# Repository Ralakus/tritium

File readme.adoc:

= Tritium Project
An open source RISC based balanced ternary computer research project

== This is a research project
This project is not fully intended to get a perfectly functional computer out to the market, but rather, it is intended to get the concept of ternary computing out to the public so more people will start researching ternary computing as an alternative to binary computing. 

== What does balanced ternary mean?
Normal computers process data in binary which means two states, a one and a zero. Ternary is similar except operating on three states. In balanced ternary, there is a negative (i), neutral (0), and positive (1) which means numbers are naturally signed thus simplifying the architecture and general logic. Ternary also has the best radix efficiency for any integer base of 1.0046 where binary is 1.0615 with base e, 1.0000 being the most efficient. A 'trit' is the ternary analogue of a bit which stores an i (-1), 0, or 1. 

== Has this been done before?
There are many projects similar to this but they either haven't gone very far, closed source and secretive, or dead. The main inspiration for this project is the Russian Setun computer, more specifically the Setun-70 which has an 18 trit word and 81 words of memory with a magnetic drum holding more memory. 

== Directory Structure
* docs - contains documentation on the project and lab results
* kicad - contains the kicad project files for each part
** components - contains all complex multigate circuits
** gates - contains all ternary gates and their panelized PCBs
** logic - contains logical schematics of circuits using logic gates instead of transistors
* library - contains all of the kicad libraries such as the footprints, spice models, and symbols

== Possible final computer variants
=== Tritium-6
A 6-trit computer that is cheap and simple to make where the instructions more closely resemble microcode rather than instructions.

==== Design Goals
* Around or less than $250 in components
* Have the ability to communicate with binary components
* Use easily sourcable parts
* One clock cycle per instruction

=== Tritium-27
A full scale computer that mirrors RISC-V in capability and instruction set.

==== Design Goals
* Around or less than $1000 in components
* Have the ability to communicate with binary components
* Use easily sourcable parts

== Current Status
The gates from OSHPark came but I've hit a bit of a time and financial crunch so I don't quite have the time to work on the physical part of the project. I'm currently working with a local college professor to write up a better ISA than the previous versions for a machine that I could follow that wouldn't be too expensive to implement. I've decided that the decoding logic for the control module may be too expensive to implement so I will see if I can use a binary EEPROM using encoded balanced ternary as a lookup table and then convert the inputs back to native balanced ternary.

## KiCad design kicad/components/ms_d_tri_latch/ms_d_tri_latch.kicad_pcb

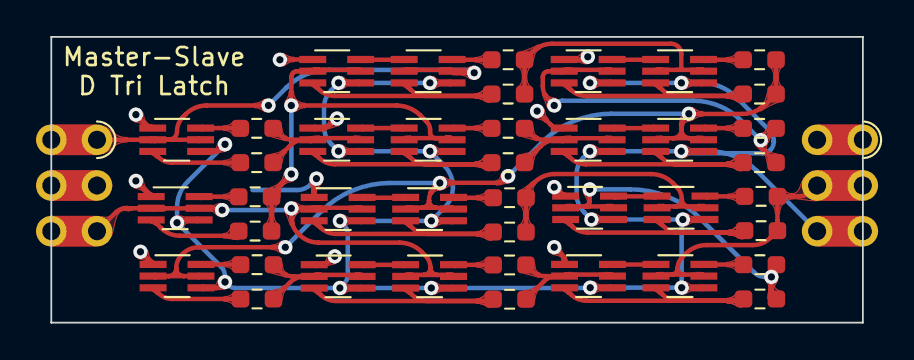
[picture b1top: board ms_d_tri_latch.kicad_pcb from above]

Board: 2 copper layers, 45.1 x 15.9 mm, 43 parts (0 on the bottom side), 45 nets.

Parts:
J1, J2: Conn_01x03; Hybrid_Castellation_1x03_P2.54
Q1, Q2, Q3, Q4, Q5, Q6, Q7, Q8, Q9, Q10, Q11, Q12, Q13, Q14, Q15, Q16, Q17, Q18, Q19: BSS8402DW-7-F; SOT-363_SC-70-6_Handsoldering
R1, R2, R3, R4, R5, R6, R7, R8, R9, R10, R11, R12, R13, R14, R15, R16, R17, R18, R19, R20, R21, R22: 12k; R_0603_1608Metric_Pad0.98x0.95mm_HandSolder

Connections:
/Inverter2/Nti: Q19.6 (D), R22.2
/Inverter2/Out: Q14.2 (G), Q14.5 (G), Q15.2 (G), Q15.5 (G), R21.2, R22.1
/Inverter2/Pti: Q19.3 (D), R21.1
/d_latch1/Antimin4/B: Q3.2 (G), Q3.5 (G), R19.2, R20.1
/d_latch1/Antimin5/Out: Q4.2 (G), Q4.5 (G), R7.2, R8.1
/d_latch1/Antimin7/B: Q18.2 (G), Q18.5 (G), R1.2, R2.1
/d_latch1/Inverter1/Nti: Q1.6 (D), R2.2
/d_latch1/Inverter1/Pti: Q1.3 (D), R1.1
/d_latch1/~Q: Q5.2 (G), Q5.5 (G), R3.2, R4.1
/d_latch/Antimin4/B: Q10.2 (G), Q10.5 (G), R17.2, R18.1
/d_latch/Antimin5/Out: Q11.2 (G), Q11.5 (G), R15.2, R16.1
/d_latch/Antimin7/B: Q16.2 (G), Q16.5 (G), R9.2, R10.1
/d_latch/Inverter1/Nti: Q8.6 (D), R10.2
/d_latch/Inverter1/Pti: Q8.3 (D), R9.1
/d_latch/Q: Q1.2 (G), Q1.5 (G), Q6.2 (G), Q6.5 (G), Q9.2 (G), Q9.5 (G), R13.2, R14.1
/d_latch/~Q: Q12.2 (G), Q12.5 (G), R11.2, R12.1
D: J1.1, Q8.2 (G), Q8.5 (G), Q13.2 (G), Q13.5 (G)
Enable: J1.3, Q7.2 (G), Q7.5 (G), Q17.2 (G), Q17.5 (G), Q19.2 (G), Q19.5 (G)
unnamed: Q2.1 (S), Q3.6 (D)
unnamed: Q2.3 (D), Q3.3 (D), R3.1
unnamed: Q2.6 (D), R4.2
unnamed: Q4.1 (S), Q5.6 (D)
unnamed: Q4.3 (D), Q5.3 (D), R5.1
unnamed: Q4.6 (D), R6.2
unnamed: Q6.1 (S), Q7.6 (D)
unnamed: Q6.3 (D), Q7.3 (D), R7.1
unnamed: Q6.6 (D), R8.2
unnamed: Q9.6 (D), R12.2
unnamed: Q9.3 (D), Q10.3 (D), R11.1
unnamed: Q9.1 (S), Q10.6 (D)
unnamed: Q11.1 (S), Q12.6 (D)
unnamed: Q11.3 (D), Q12.3 (D), R13.1
unnamed: Q11.6 (D), R14.2
unnamed: Q13.1 (S), Q14.6 (D)
unnamed: Q13.3 (D), Q14.3 (D), R15.1
unnamed: Q13.6 (D), R16.2
unnamed: Q15.1 (S), Q16.6 (D)
unnamed: Q15.3 (D), Q16.3 (D), R17.1
unnamed: Q15.6 (D), R18.2
unnamed: Q17.1 (S), Q18.6 (D)
unnamed: Q17.3 (D), Q18.3 (D), R19.1
unnamed: Q17.6 (D), R20.2
Q: J2.2, Q2.2 (G), Q2.5 (G), R5.2, R6.1
VDD: J2.3, Q1.4 (S), Q2.4 (S), Q3.4 (S), Q4.4 (S), Q5.4 (S), Q6.4 (S), Q7.4 (S), Q8.4 (S), Q9.4 (S), Q10.4 (S), Q11.4 (S), Q12.4 (S), Q13.4 (S), Q14.4 (S), Q15.4 (S), Q16.4 (S), Q17.4 (S), Q18.4 (S), Q19.4 (S)
VSS: J1.2, J2.1, Q1.1 (S), Q3.1 (S), Q5.1 (S), Q7.1 (S), Q8.1 (S), Q10.1 (S), Q12.1 (S), Q14.1 (S), Q16.1 (S), Q18.1 (S), Q19.1 (S)

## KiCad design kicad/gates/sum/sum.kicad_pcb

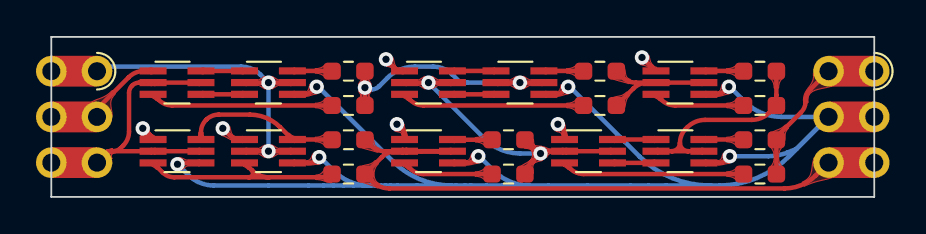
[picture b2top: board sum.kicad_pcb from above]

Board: 2 copper layers, 45.7 x 8.9 mm, 24 parts (0 on the bottom side), 28 nets.

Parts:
J1, J2: Conn_01x03; Hybrid_Castellation_1x03_P2.54
Q1, Q2, Q3, Q4, Q5, Q6, Q7, Q8, Q9, Q10: BSS8402DW-7-F; SOT-363_SC-70-6_Handsoldering
R1, R2, R3, R4, R5, R6, R7, R8, R9, R10, R11, R12: 12k; R_0603_1608Metric_Pad0.98x0.95mm_HandSolder

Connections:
/Inverter BL/Nti: Q8.6 (D), R10.2
/Inverter BL/Out: Q4.2 (G), Q4.5 (G), Q6.2 (G), Q6.5 (G), R9.2, R10.1
/Inverter BL/Pti: Q8.3 (D), R9.1
/Inverter M/In: Q7.2 (G), Q7.5 (G), R3.2, R4.1
/Inverter M/Nti: Q7.6 (D), R8.2
/Inverter M/Out: Q5.2 (G), Q5.5 (G), R7.2, R8.1
/Inverter M/Pti: Q7.3 (D), R7.1
/NAny M/A: Q3.2 (G), Q3.5 (G), R1.2, R2.1
A: J1.1, Q1.2 (G), Q1.5 (G), Q9.2 (G), Q9.5 (G)
B: J1.3, Q2.2 (G), Q2.5 (G), Q10.2 (G), Q10.5 (G)
unnamed: Q1.1 (S), Q2.6 (D)
unnamed: Q1.3 (D), Q2.4 (S)
unnamed: Q1.6 (D), R2.2
unnamed: Q2.3 (D), R1.1
unnamed: Q3.1 (S), Q4.6 (D)
unnamed: Q3.3 (D), Q4.4 (S)
unnamed: Q3.6 (D), R4.2
unnamed: Q4.3 (D), R3.1
unnamed: Q5.1 (S), Q6.6 (D)
unnamed: Q5.3 (D), Q6.4 (S)
unnamed: Q5.6 (D), R6.2
unnamed: Q6.3 (D), R5.1
unnamed: Q9.3 (D), Q10.3 (D), R11.1
unnamed: Q9.6 (D), Q10.6 (D), R12.2
Sum: J2.1, R5.2, R6.1
VDD: J2.2, Q1.4 (S), Q3.4 (S), Q5.4 (S), Q7.4 (S), Q8.4 (S), Q9.4 (S), Q10.4 (S)
VSS: J1.2, Q2.1 (S), Q4.1 (S), Q6.1 (S), Q7.1 (S), Q8.1 (S), Q9.1 (S), Q10.1 (S)
~Carry: J2.3, Q8.2 (G), Q8.5 (G), R11.2, R12.1

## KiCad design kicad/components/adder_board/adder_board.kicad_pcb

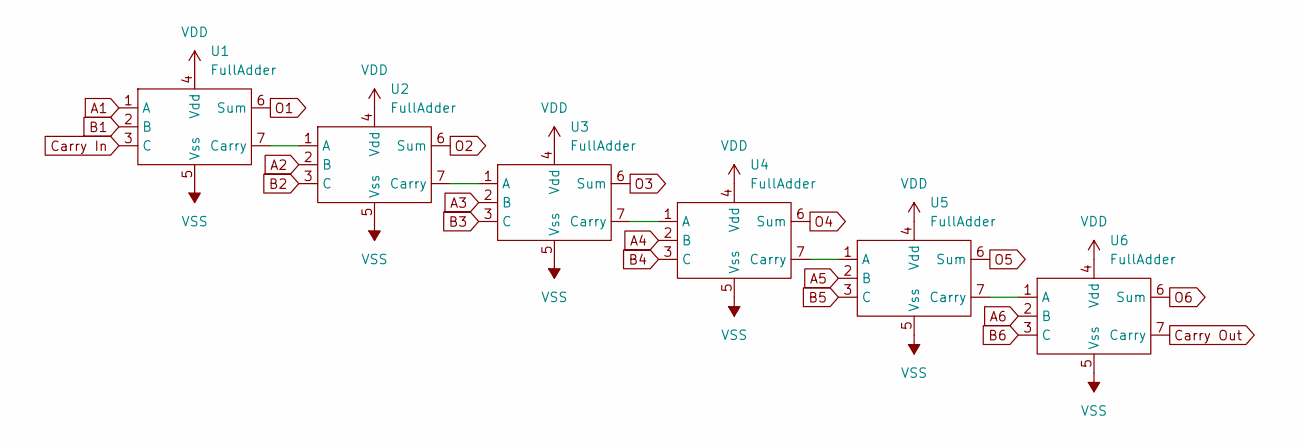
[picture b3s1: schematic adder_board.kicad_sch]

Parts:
U1, U2, U3, U4, U5, U6: FullAdder

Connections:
A1: U1.1 (A)
A2: U2.2 (B)
A3: U3.2 (B)
A4: U4.2 (B)
A5: U5.2 (B)
A6: U6.2 (B)
B1: U1.2 (B)
B2: U2.3 (C)
B3: U3.3 (C)
B4: U4.3 (C)
B5: U5.3 (C)
B6: U6.3 (C)
Carry In: U1.3 (C)
Carry Out: U6.7 (Carry)
unnamed: U1.7 (Carry), U2.1 (A)
unnamed: U2.7 (Carry), U3.1 (A)
unnamed: U3.7 (Carry), U4.1 (A)
unnamed: U4.7 (Carry), U5.1 (A)
unnamed: U5.7 (Carry), U6.1 (A)
O1: U1.6 (Sum)
O2: U2.6 (Sum)
O3: U3.6 (Sum)
O4: U4.6 (Sum)
O5: U5.6 (Sum)
O6: U6.6 (Sum)
VDD: U1.4 (Vdd), U2.4 (Vdd), U3.4 (Vdd), U4.4 (Vdd), U5.4 (Vdd), U6.4 (Vdd)
VSS: U1.5 (Vss), U2.5 (Vss), U3.5 (Vss), U4.5 (Vss), U5.5 (Vss), U6.5 (Vss)

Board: 2 copper layers, 6 parts (0 on the bottom side), 7 nets, no tracks yet.

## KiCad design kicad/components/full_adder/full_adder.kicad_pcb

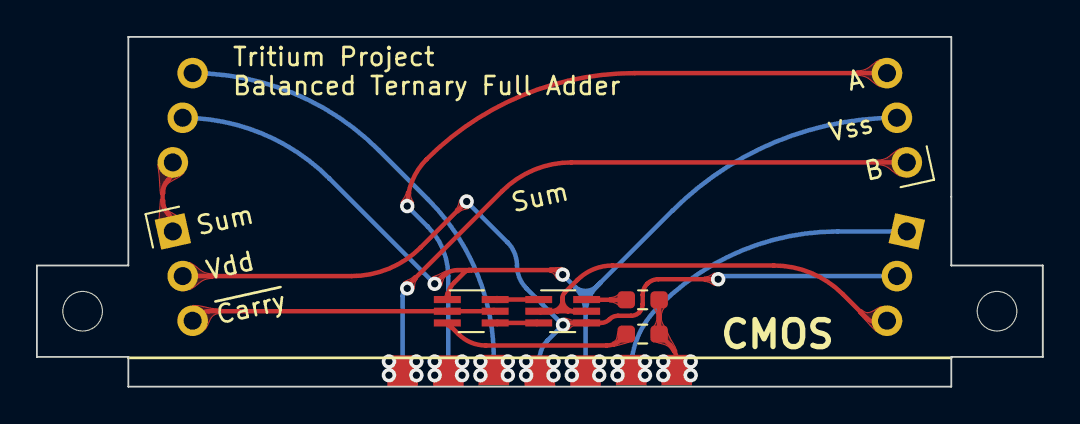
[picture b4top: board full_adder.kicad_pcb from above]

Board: 2 copper layers, 55.9 x 19.4 mm, 6 parts (1 on the bottom side), 10 nets.

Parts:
Q1, Q2: BSS8402DW-7-F; SOT-363_SC-70-6_Handsoldering
R1, R2: 12k; R_0603_1608Metric_Pad0.98x0.95mm_HandSolder
U1, U2: Sum

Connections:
/NAny/A: Q1.2 (G), Q1.5 (G), U2.3 (~Carry)
/NAny/B: Q2.2 (G), Q2.5 (G), U1.3 (~Carry)
Carry: R1.2, R2.1
unnamed: Q1.1 (S), Q2.6 (D)
unnamed: Q1.3 (D), Q2.4 (S)
unnamed: Q1.6 (D), R2.2
unnamed: Q2.3 (D), R1.1
unnamed: U1.1 (Sum), U2.6 (B)
VDD: Q1.4 (S), U1.2 (Vdd), U2.2 (Vdd)
VSS: Q2.1 (S), U1.5 (Vss), U2.5 (Vss)

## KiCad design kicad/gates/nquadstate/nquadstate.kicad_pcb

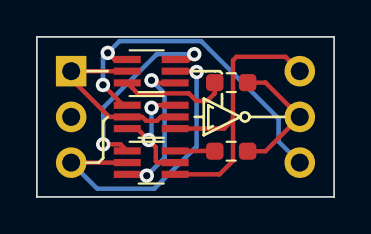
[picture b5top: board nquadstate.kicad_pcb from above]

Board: 2 copper layers, 16.5 x 8.9 mm, 7 parts (0 on the bottom side), 10 nets.

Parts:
J1, J2: Conn_01x03; PinHeader_1x03_P2.54mm_Vertical_NoSilkscreen
Q1, Q2, Q3: BSS8402DW-7-F; SOT-363_SC-70-6_Handsoldering
R1, R2: 12k; R_0603_1608Metric_Pad0.98x0.95mm_HandSolder

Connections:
Gate: J1.1, Q1.2 (G), Q1.5 (G), Q3.2 (G)
In: J1.3, Q2.2 (G), Q3.5 (G)
unnamed: Q1.3 (D), Q1.6 (D), Q2.5 (G)
unnamed: Q2.1 (S), Q3.6 (D)
unnamed: Q2.3 (D), Q3.4 (S)
unnamed: Q2.6 (D), R2.2
unnamed: Q3.3 (D), R1.1
Out: J2.2, R1.2, R2.1
VDD: J2.1, Q1.4 (S), Q2.4 (S)
VSS: J2.3, Q1.1 (S), Q3.1 (S)

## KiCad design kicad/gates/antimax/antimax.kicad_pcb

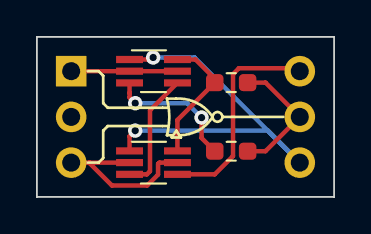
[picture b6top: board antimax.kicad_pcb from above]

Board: 2 copper layers, 16.5 x 8.9 mm, 6 parts (0 on the bottom side), 8 nets.

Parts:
J1, J2: Conn_01x03; PinHeader_1x03_P2.54mm_Vertical_NoSilkscreen
Q1, Q2: BSS8402DW-7-F; SOT-363_SC-70-6_Handsoldering
R1, R2: 12k; R_0603_1608Metric_Pad0.98x0.95mm_HandSolder

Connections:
A: J1.3, Q1.2 (G), Q1.5 (G)
B: J1.1, Q2.2 (G), Q2.5 (G)
unnamed: Q1.3 (D), Q2.4 (S)
unnamed: Q1.6 (D), Q2.6 (D), R2.2
unnamed: Q2.3 (D), R1.1
Out: J2.2, R1.2, R2.1
VDD: J2.1, Q1.4 (S)
VSS: J2.3, Q1.1 (S), Q2.1 (S)

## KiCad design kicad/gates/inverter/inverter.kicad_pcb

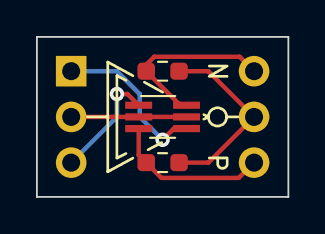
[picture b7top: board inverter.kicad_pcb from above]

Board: 2 copper layers, 14.0 x 8.9 mm, 5 parts (0 on the bottom side), 6 nets.

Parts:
J1, J2: Conn_01x03; PinHeader_1x03_P2.54mm_Vertical_NoSilkscreen
Q1: BSS8402DW-7-F; SOT-363_SC-70-6_Handsoldering
R1, R2: 12k; R_0603_1608Metric_Pad0.98x0.95mm_HandSolder

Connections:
In: J1.2, Q1.2 (G), Q1.5 (G)
Nti: J2.1, Q1.6 (D), R2.2
Out: J2.2, R1.2, R2.1
Pti: J2.3, Q1.3 (D), R1.1
VDD: J1.1, Q1.4 (S)
VSS: J1.3, Q1.1 (S)

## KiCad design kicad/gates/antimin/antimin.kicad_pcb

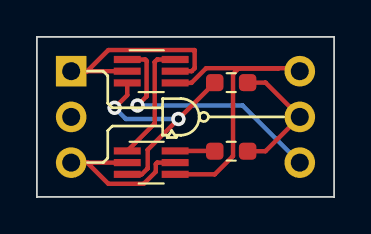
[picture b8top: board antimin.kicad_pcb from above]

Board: 2 copper layers, 16.5 x 8.9 mm, 6 parts (0 on the bottom side), 8 nets.

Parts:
J1, J2: Conn_01x03; PinHeader_1x03_P2.54mm_Vertical_NoSilkscreen
Q1, Q2: BSS8402DW-7-F; SOT-363_SC-70-6_Handsoldering
R1, R2: 12k; R_0603_1608Metric_Pad0.98x0.95mm_HandSolder

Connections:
A: J1.3, Q1.2 (G), Q1.5 (G)
B: J1.1, Q2.2 (G), Q2.5 (G)
unnamed: Q1.1 (S), Q2.6 (D)
unnamed: Q1.3 (D), Q2.3 (D), R1.1
unnamed: Q1.6 (D), R2.2
Out: J2.2, R1.2, R2.1
VDD: J2.1, Q1.4 (S), Q2.4 (S)
VSS: J2.3, Q2.1 (S)

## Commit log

2020-12-07 binary converter
2020-12-18 ternary adders, switches, and cyclers
2020-12-18 remove nconensus gate from sum gate, removed .sch-bak and cache files
2020-12-18 add .gitignore
2020-12-18 lowered transistor count for sum gate
2020-12-18 added flat schematic for full adder
2020-12-20 added pcbs for each gate
2020-12-20 updated isa and added memory map documentation
2020-12-23 added KiCad library for ternary gates and went from header pins and sockets to castellated edge pcbs
2020-12-27 added ngspice models for each gate symbol
2020-12-27 updated readme.md and materials.md
2020-12-27 update readme.md to include current project status
2020-12-28 added edge triggered triflop
2020-12-28 added block diagram architecture
2021-01-01 re-organized project directory and started work on ALU pcb
2021-01-01 started pure ternary alu
2021-01-03 designed alu schematic
2021-01-03 layed out alu pcb
2021-01-03 routed adder traces
2021-01-04 remake alu to be modular and updated isa to add control register and memory paging
2021-01-04 change bit to trit
2021-01-07 bss84 drain and source flipped
2021-01-09 tested rev.0 pcbs and added results to doc
2021-01-09 fixed table alignment in test results
2021-01-09 added expected results to rev.0 pcb test
2021-01-09 udpated readme.md
2021-01-10 completed adder module for alu
2021-01-10 completed adder module schematics
2021-01-10 moved overall system schematic to architecture folder
2021-01-16 started fast addition experiments and tritium-6 architecture
2021-01-16 updated tritium-6 isa to include basic stack operations
2021-01-16 changed incrementing and decrementing stack pointer to stack instruction
2021-01-17 moved documentation from markdown to asciidoc
2021-01-17 fixed errors in tritium-9 documentation
2021-02-03 updated status in readme.adoc
2021-02-08 added gate name to rev.2 pcbs and added clip gate
2021-02-08 added rev.2 gerbers
2021-04-13 started tritium 6 emulator and fixed tritium 6 isa spec
2021-04-17 updated tritium-6 isa to include tritshifting and started bugfixing emulator
2021-04-17 fixed typos in tritium-6 isa and emulator
2021-04-17 added more information to some instructions in tritium-6 isa
2021-04-30 restructued project directory and added schematic pdfs
2021-04-30 updated tritium-6 emulator to use rust traits
2021-05-17 added rev.3 gates
2021-05-19 updated antimin rev.3 pcb to fix board size
2021-05-20 updated readme.adoc
2021-05-20 updated readme.adoc again
2021-05-20 updated readme.adoc yet again
2021-05-20 updated materials.adoc
2022-08-05 project cleanup and restructure
2022-08-06 fixed sum logic gate schematic and simulation
2022-08-06 updated inverter logic symbol to match art on pcb and updated readme
2022-08-06 added power supply to materials list
2022-08-08 created sum gate pcb and full adder pcb and analog consensus, min, and max logic gates
2022-08-08 deleted kicad cache files
2022-08-08 updated .gitignore to ignore cache files
2023-03-02 Update readme.adoc with current project status. Created master-slave D tri-latch gate
